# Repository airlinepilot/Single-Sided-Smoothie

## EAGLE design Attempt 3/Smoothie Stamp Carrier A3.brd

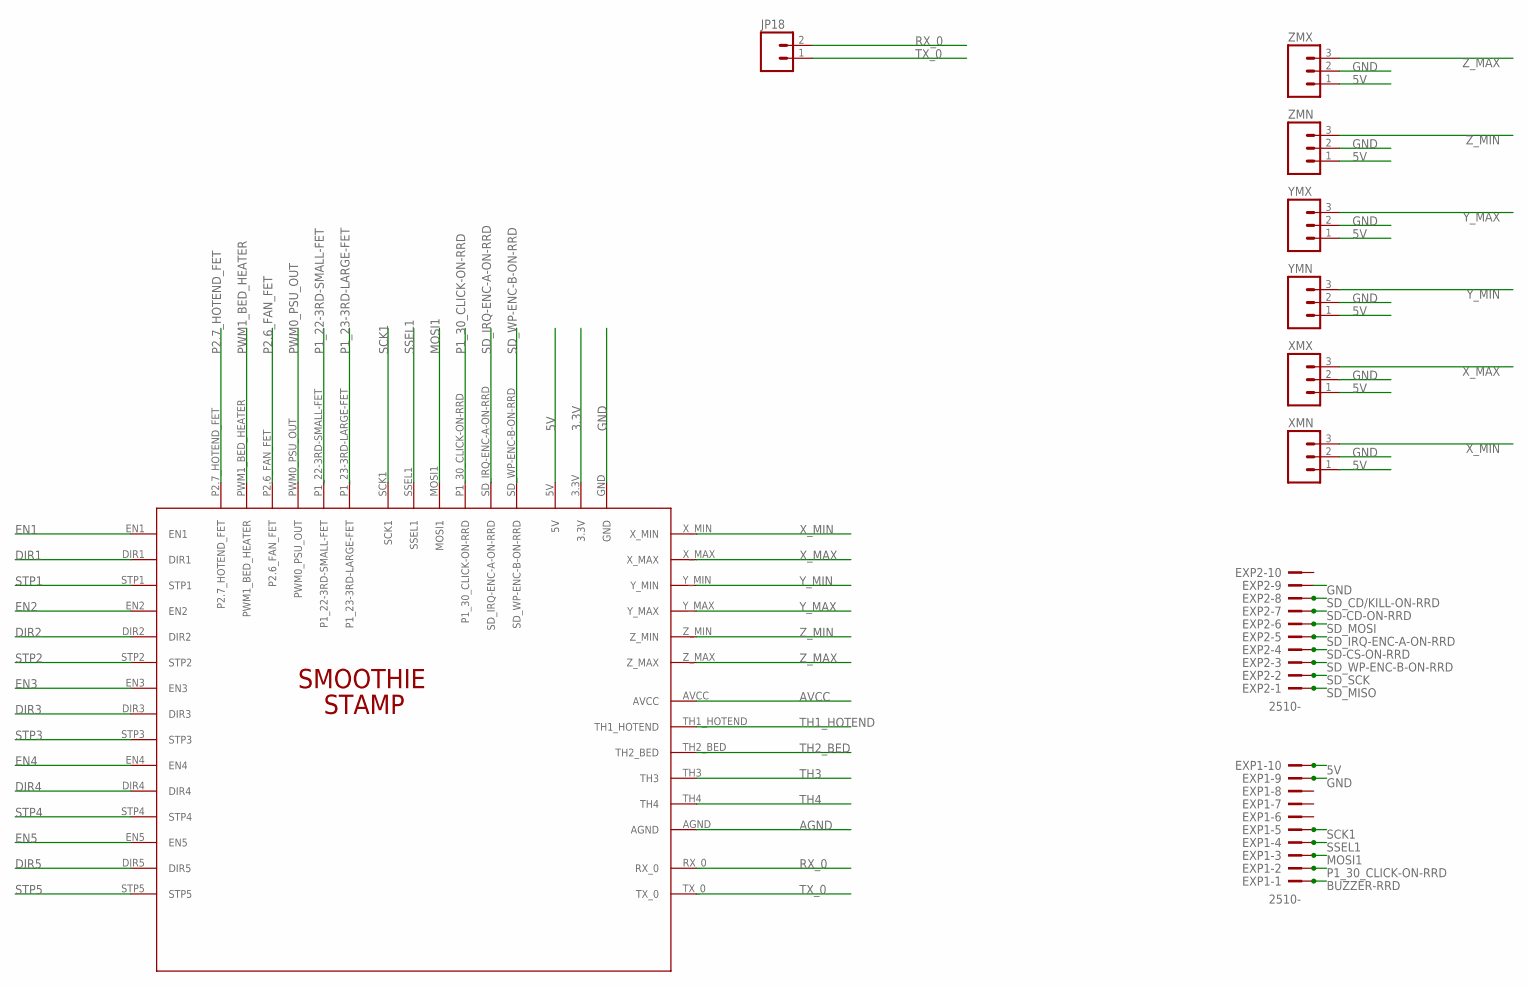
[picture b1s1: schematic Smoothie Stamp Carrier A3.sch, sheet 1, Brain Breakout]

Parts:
EXP1, EXP2: 2510-; PAK100/2500-10
JP18: M02LOCK; 1X02_LOCK
U$1: SMOOTHIE-STAMPSMOOTHIE-STAMP-PTH; SMOOTHIE-STAMP-PTH
XMN: M03LOCK; 1X03_LOCK
XMX: M03LOCK; 1X03_LOCK
YMN: M03LOCK; 1X03_LOCK
YMX: M03LOCK; 1X03_LOCK
ZMN: M03LOCK; 1X03_LOCK
ZMX: M03LOCK; 1X03_LOCK

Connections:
3.3V: U$1.3.3V; also elsewhere on the board
5V: EXP1.10, U$1.5V, XMN.1, XMX.1, YMN.1, YMX.1, ZMN.1, ZMX.1
AGND: U$1.AGND; also elsewhere on the board
AVCC: U$1.AVCC; also elsewhere on the board
BUZZER-RRD: EXP1.1
DIR1: U$1.DIR1; also elsewhere on the board
DIR2: U$1.DIR2; also elsewhere on the board
DIR3: U$1.DIR3; also elsewhere on the board
DIR4: U$1.DIR4; also elsewhere on the board
DIR5: U$1.DIR5; also elsewhere on the board
EN1: U$1.EN1; also elsewhere on the board
EN2: U$1.EN2; also elsewhere on the board
EN3: U$1.EN3; also elsewhere on the board
EN4: U$1.EN4; also elsewhere on the board
EN5: U$1.EN5; also elsewhere on the board
GND: EXP1.9, EXP2.9, U$1.GND, XMN.2, XMX.2, YMN.2, YMX.2, ZMN.2, ZMX.2; also elsewhere on the board
MOSI1: EXP1.3, U$1.MOSI1
P1_22-3RD-SMALL-FET: U$1.P1_22-3RD-SMALL-FET; also elsewhere on the board
P1_23-3RD-LARGE-FET: U$1.P1_23-3RD-LARGE-FET; also elsewhere on the board
P1_30_CLICK-ON-RRD: EXP1.2, U$1.P1_30_CLICK-ON-RRD
P2.6_FAN_FET: U$1.P2.6_FAN_FET; also elsewhere on the board
P2.7_HOTEND_FET: U$1.P2.7_HOTEND_FET; also elsewhere on the board
PWM0_PSU_OUT: U$1.PWM0_PSU_OUT; also elsewhere on the board
PWM1_BED_HEATER: U$1.PWM1_BED_HEATER; also elsewhere on the board
RX_0: JP18.2, U$1.RX_0
SCK1: EXP1.5, U$1.SCK1
SD-CD-ON-RRD: EXP2.7
SD-CS-ON-RRD: EXP2.4
SD_CD/KILL-ON-RRD: EXP2.8
SD_IRQ-ENC-A-ON-RRD: EXP2.5, U$1.SD_IRQ-ENC-A-ON-RRD
SD_MISO: EXP2.1
SD_MOSI: EXP2.6
SD_SCK: EXP2.2
SD_WP-ENC-B-ON-RRD: EXP2.3, U$1.SD_WP-ENC-B-ON-RRD
SSEL1: EXP1.4, U$1.SSEL1
STP1: U$1.STP1; also elsewhere on the board
STP2: U$1.STP2; also elsewhere on the board
STP3: U$1.STP3; also elsewhere on the board
STP4: U$1.STP4; also elsewhere on the board
STP5: U$1.STP5; also elsewhere on the board
TH1_HOTEND: U$1.TH1_HOTEND; also elsewhere on the board
TH2_BED: U$1.TH2_BED; also elsewhere on the board
TH3: U$1.TH3; also elsewhere on the board
TH4: U$1.TH4; also elsewhere on the board
TX_0: JP18.1, U$1.TX_0
X_MAX: U$1.X_MAX, XMX.3
X_MIN: U$1.X_MIN, XMN.3
Y_MAX: U$1.Y_MAX, YMX.3
Y_MIN: U$1.Y_MIN, YMN.3
Z_MAX: U$1.Z_MAX, ZMX.3
Z_MIN: U$1.Z_MIN, ZMN.3

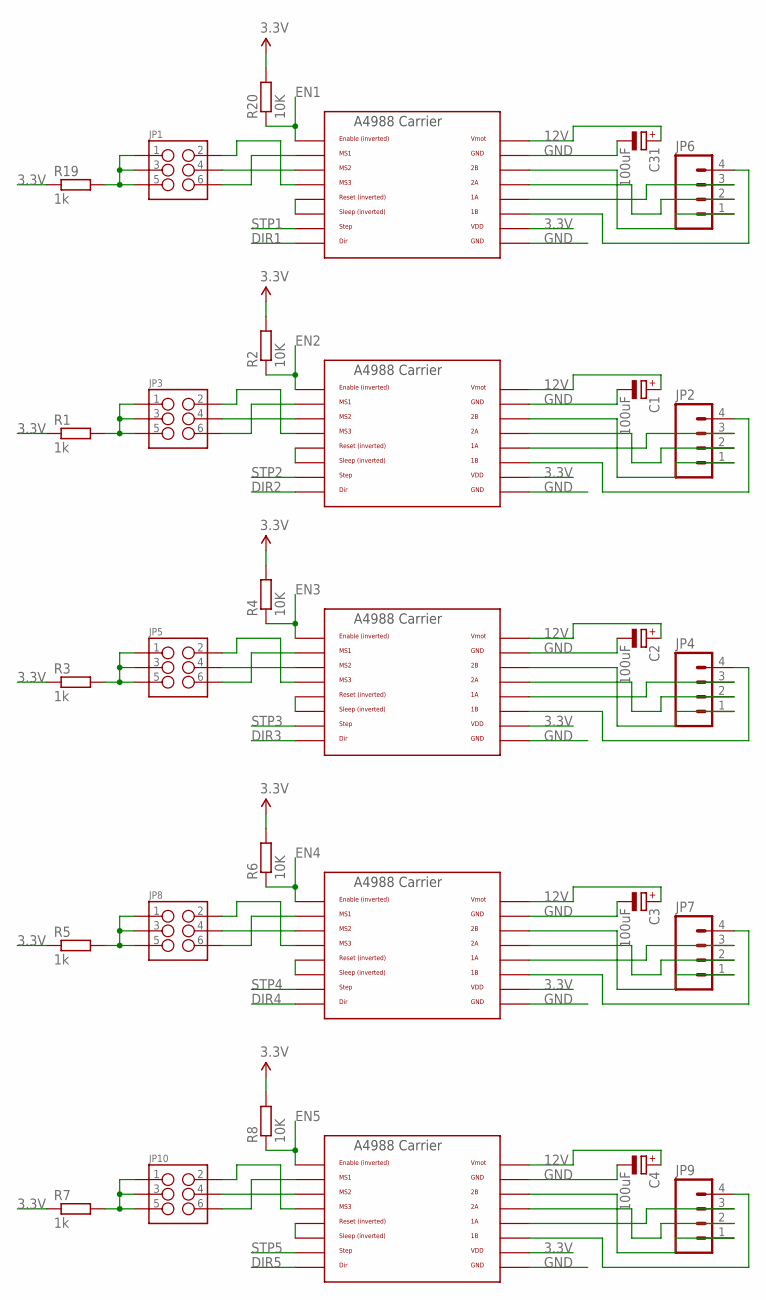
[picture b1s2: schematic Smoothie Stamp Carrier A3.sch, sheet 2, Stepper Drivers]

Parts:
C1, C2, C3, C4, C31: 100uF; E3,5-8
JP1, JP3, JP5, JP8, JP10: M03X22X3_SILK_MALE_PTH; 2X3
JP2, JP4, JP6, JP7, JP9: M04POLAR_LOCK; MOLEX-1X4_LOCK
R1, R3, R5, R7, R19: 1k; 0204V
R2, R4, R6, R8, R20: 10K; 0204V
U$2, U$3, U$4, U$5, U$6: POLOLU_A4983CARRIER; A4988BREAKOUT

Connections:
3.3V: R1.1, R2.2, R3.1, R4.2, R5.1, R6.2, R7.1, R8.2, R19.1, R20.2, U$2.VDD, U$3.VDD, U$4.VDD, U$5.VDD, U$6.VDD; also elsewhere on the board
12V: C1.+, C2.+, C3.+, C4.+, C31.+, U$2.VMOT, U$3.VMOT, U$4.VMOT, U$5.VMOT, U$6.VMOT; also elsewhere on the board
DIR1: U$2.DIR; also elsewhere on the board
DIR2: U$3.DIR; also elsewhere on the board
DIR3: U$4.DIR; also elsewhere on the board
DIR4: U$5.DIR; also elsewhere on the board
DIR5: U$6.DIR; also elsewhere on the board
EN1: R20.1, U$2.EN; also elsewhere on the board
EN2: R2.1, U$3.EN; also elsewhere on the board
EN3: R4.1, U$4.EN; also elsewhere on the board
EN4: R6.1, U$5.EN; also elsewhere on the board
EN5: R8.1, U$6.EN; also elsewhere on the board
GND: C1.-, C2.-, C3.-, C4.-, C31.-, U$2.GND, U$2.GND@0 (GND), U$3.GND, U$3.GND@0 (GND), U$4.GND, U$4.GND@0 (GND), U$5.GND, U$5.GND@0 (GND), U$6.GND, U$6.GND@0 (GND); also elsewhere on the board
unnamed: JP1.6, U$2.MS1
unnamed: JP1.2, U$2.MS3
unnamed: JP1.4, U$2.MS2
unnamed: JP1.1, JP1.3, JP1.5, R19.2
unnamed: JP6.4, U$2.1B
unnamed: JP6.3, U$2.1A
unnamed: JP6.2, U$2.2A
unnamed: JP6.1, U$2.2B
unnamed: U$3.RST, U$3.SLP (SLEEP)
unnamed: JP3.1, JP3.3, JP3.5, R1.2
unnamed: JP3.6, U$3.MS1
unnamed: JP3.2, U$3.MS3
unnamed: JP3.4, U$3.MS2
unnamed: JP2.4, U$3.1B
unnamed: JP2.3, U$3.1A
unnamed: JP2.2, U$3.2A
unnamed: JP2.1, U$3.2B
unnamed: U$4.RST, U$4.SLP (SLEEP)
unnamed: JP5.1, JP5.3, JP5.5, R3.2
unnamed: JP5.6, U$4.MS1
unnamed: JP5.2, U$4.MS3
unnamed: JP5.4, U$4.MS2
unnamed: JP4.4, U$4.1B
unnamed: JP4.3, U$4.1A
unnamed: JP4.2, U$4.2A
unnamed: JP4.1, U$4.2B
unnamed: U$5.RST, U$5.SLP (SLEEP)
unnamed: JP8.1, JP8.3, JP8.5, R5.2
unnamed: JP8.6, U$5.MS1
unnamed: JP8.2, U$5.MS3
unnamed: JP8.4, U$5.MS2
unnamed: JP7.4, U$5.1B
unnamed: JP7.3, U$5.1A
unnamed: JP7.2, U$5.2A
unnamed: U$2.RST, U$2.SLP (SLEEP)
unnamed: JP7.1, U$5.2B
unnamed: U$6.RST, U$6.SLP (SLEEP)
unnamed: JP10.1, JP10.3, JP10.5, R7.2
unnamed: JP10.6, U$6.MS1
unnamed: JP10.2, U$6.MS3
unnamed: JP10.4, U$6.MS2
unnamed: JP9.4, U$6.1B
unnamed: JP9.3, U$6.1A
unnamed: JP9.2, U$6.2A
unnamed: JP9.1, U$6.2B
STP1: U$2.STEP; also elsewhere on the board
STP2: U$3.STEP; also elsewhere on the board
STP3: U$4.STEP; also elsewhere on the board
STP4: U$5.STEP; also elsewhere on the board
STP5: U$6.STEP; also elsewhere on the board

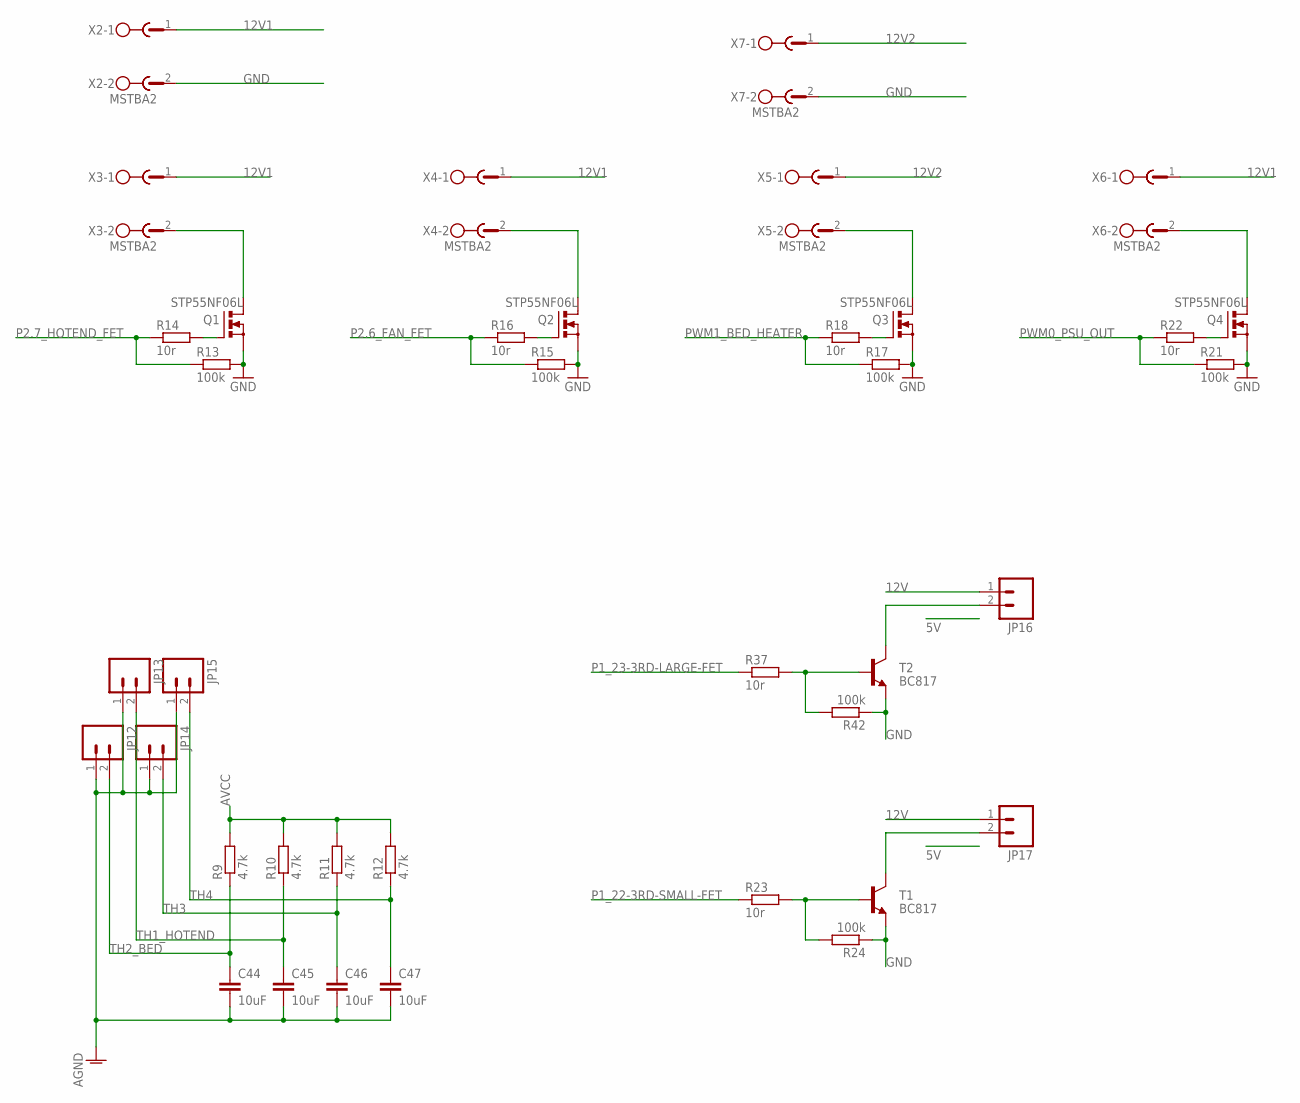
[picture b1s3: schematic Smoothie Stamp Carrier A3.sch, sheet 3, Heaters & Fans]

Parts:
C44, C45, C46, C47: 10uF; C050-025X075
JP12, JP13, JP14, JP15: M02PTH; 1X02
JP16, JP17: M02LOCK; 1X02_LOCK
Q1, Q2, Q3, Q4: STP55NF06L; TO220BV
R9, R10, R11, R12: 4.7k; 0207/5V
R13, R15, R17, R21, R24, R42: 100k; 0204V
R14, R16, R18, R22, R23, R37: 10r; 0204V
T1, T2: BC817; TO-92
X2, X3, X4, X5, X6, X7: MSTBA2

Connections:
12V: JP16.1, JP17.1; also elsewhere on the board
12V1: X2.1, X3.1, X4.1, X6.1
12V2: X5.1, X7.1
AGND: C44.2, C45.2, C46.2, C47.2, JP12.1, JP13.1, JP14.1, JP15.1; also elsewhere on the board
AVCC: R9.2, R10.2, R11.2, R12.2; also elsewhere on the board
GND: Q1.S, Q2.S, Q3.S, Q4.S, R13.2, R15.2, R17.2, R21.2, R24.1, R42.1, T1.1 (E), T2.1 (E), X2.2, X7.2; also elsewhere on the board
unnamed: Q1.D, X3.2
unnamed: Q2.G, R16.2
unnamed: Q2.D, X4.2
unnamed: Q3.G, R18.2
unnamed: Q3.D, X5.2
unnamed: Q4.G, R22.2
unnamed: Q4.D, X6.2
unnamed: Q1.G, R14.2
unnamed: JP16.2, T2.3 (C)
unnamed: R37.2, R42.2, T2.2 (B)
unnamed: JP17.2, T1.3 (C)
unnamed: R23.2, R24.2, T1.2 (B)
P1_22-3RD-SMALL-FET: R23.1; also elsewhere on the board
P1_23-3RD-LARGE-FET: R37.1; also elsewhere on the board
P2.6_FAN_FET: R15.1, R16.1; also elsewhere on the board
P2.7_HOTEND_FET: R13.1, R14.1; also elsewhere on the board
PWM0_PSU_OUT: R21.1, R22.1; also elsewhere on the board
PWM1_BED_HEATER: R17.1, R18.1; also elsewhere on the board
TH1_HOTEND: C45.1, JP13.2, R10.1; also elsewhere on the board
TH2_BED: C44.1, JP12.2, R9.1; also elsewhere on the board
TH3: C46.1, JP14.2, R11.1; also elsewhere on the board
TH4: C47.1, JP15.2, R12.1; also elsewhere on the board

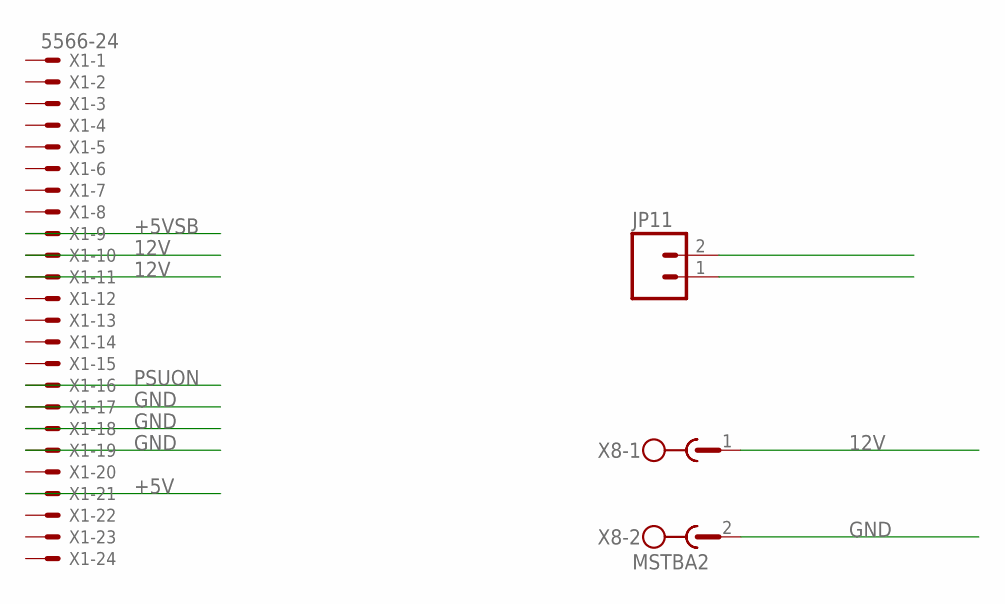
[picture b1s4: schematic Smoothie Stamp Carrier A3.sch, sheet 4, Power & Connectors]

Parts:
JP11: M02LOCK; 1X02_LOCK
X1: 5566-24
X8: MSTBA2

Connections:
12V: X1.10, X1.11, X8.1; also elsewhere on the board
+5V: X1.21
+5VSB: X1.9
GND: JP11.1, X1.17, X1.18, X1.19, X8.2; also elsewhere on the board
PSUON: JP11.2, X1.16

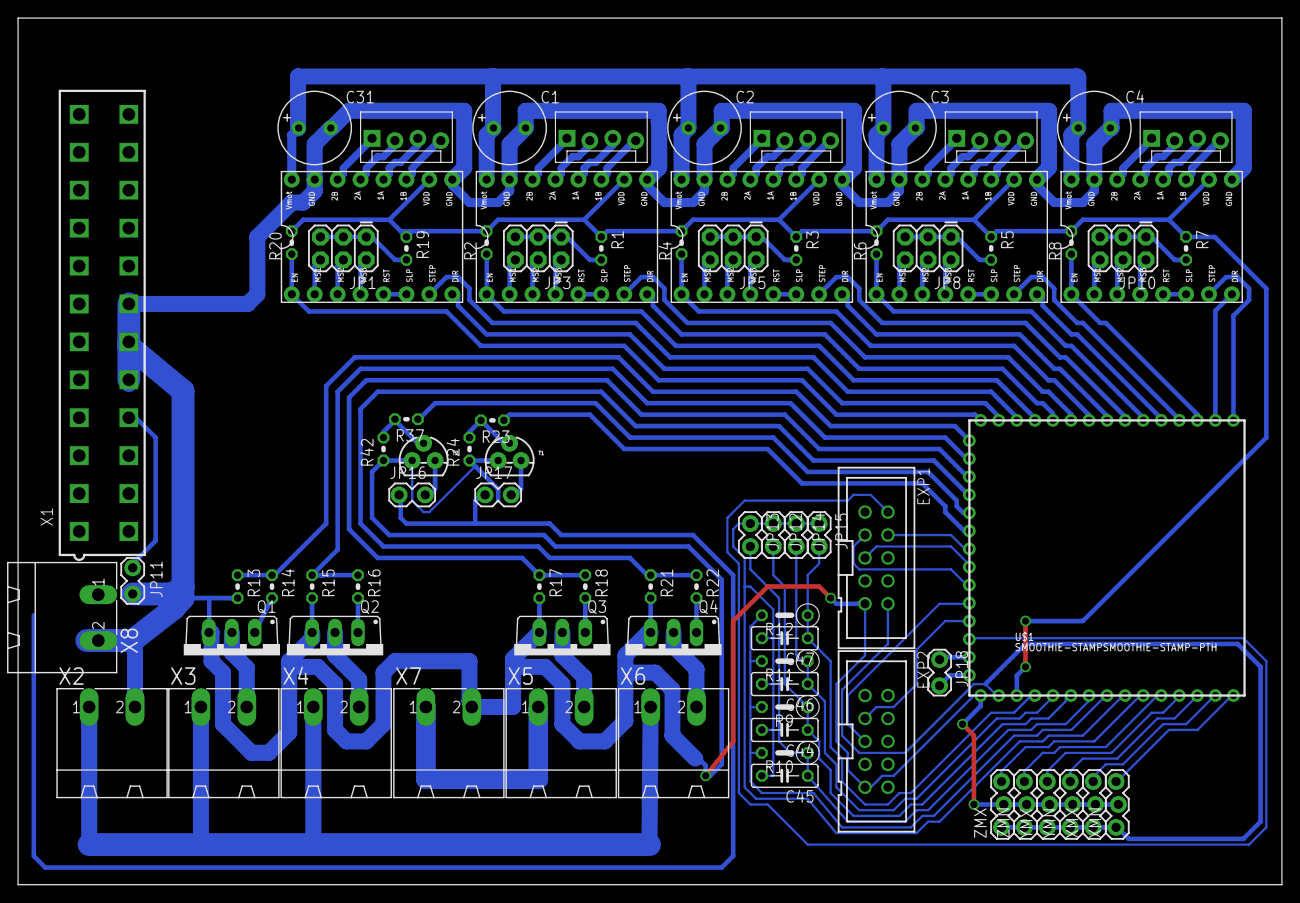
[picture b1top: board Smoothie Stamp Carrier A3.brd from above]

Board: 2 copper layers, 140.0 x 96.0 mm, 81 parts (0 on the bottom side), 105 nets.

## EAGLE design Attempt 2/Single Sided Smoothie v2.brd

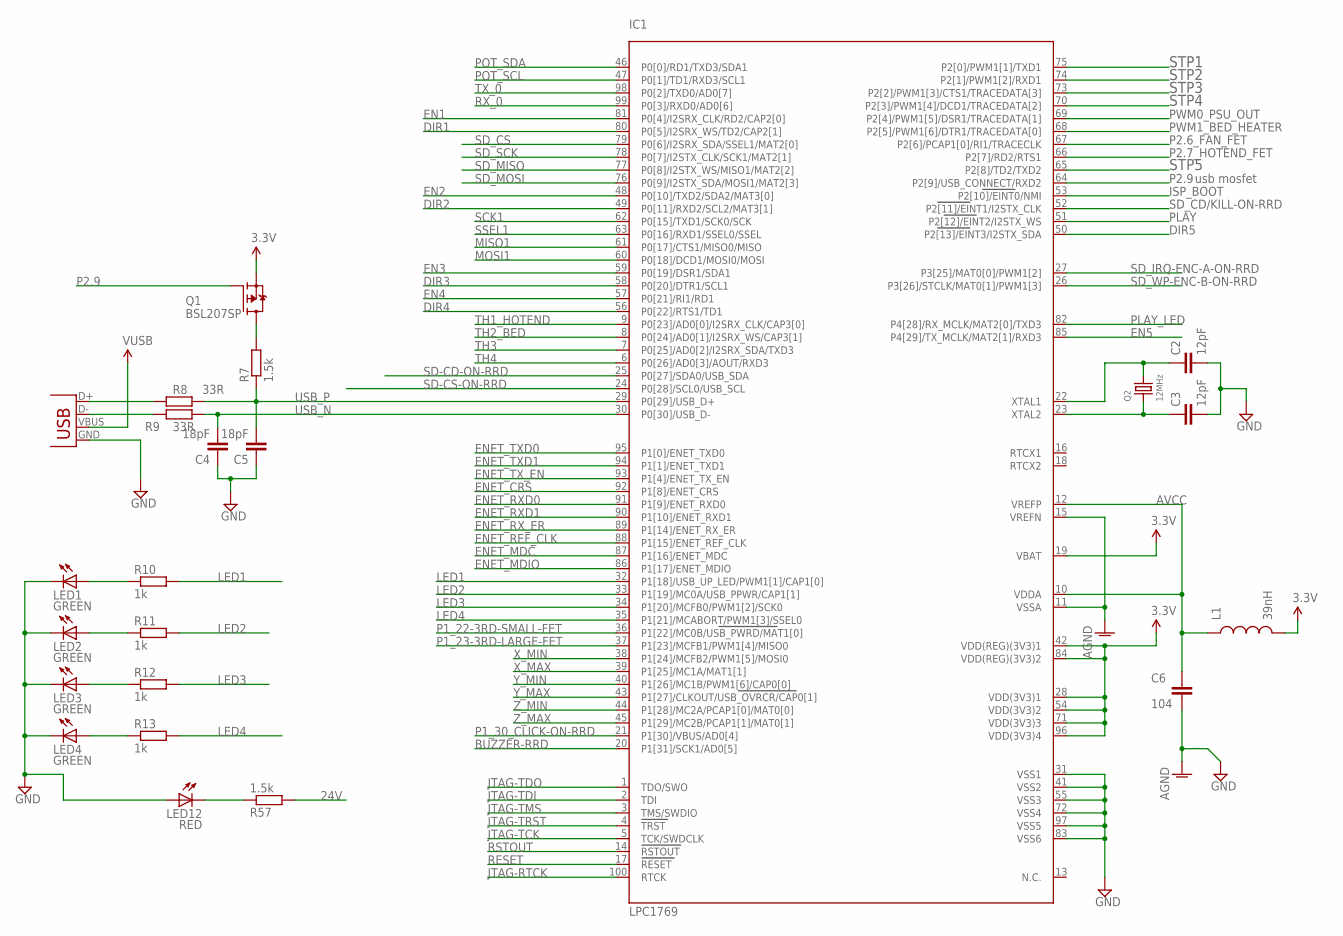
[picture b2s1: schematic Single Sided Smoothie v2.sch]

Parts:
C2, C3: 12pF; C0603
C4, C5: 18pF; C0603
C6: 104; C0603
IC1: LPC1769; LQFP100
L1: 39nH; 0603
LED1, LED2, LED3, LED4: GREEN; SML0603
LED12: RED; SML0603
Q1: BSL207SP; SC74_INFINEON
Q2: 12MHz; CRYSTAL_3.2X2.5
R7, R57: 1.5k; R0603
R8, R9: 33R; R0603
R10, R11, R12, R13: 1k; R0603
X14: USBPTH; USB-B-PTH

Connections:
3.3V: IC1.19 (VBAT), IC1.28 (VDD(3V3)1), IC1.42 (VDD(REG)(3V3)1), IC1.54 (VDD(3V3)2), IC1.71 (VDD(3V3)3), IC1.84 (VDD(REG)(3V3)2), IC1.96 (VDD(3V3)4), L1.2, Q1.4 (S)
24V: R57.2
AGND: C6.2, IC1.11 (VSSA), IC1.15 (VREFN)
AVCC: C6.1, IC1.10 (VDDA), IC1.12 (VREFP), L1.1
BUZZER-RRD: IC1.20 (P1[31]/SCK1/AD0[5])
DIR1: IC1.80 (P0[5]/I2SRX_WS/TD2/CAP2[1])
DIR2: IC1.49 (P0[11]/RXD2/SCL2/MAT3[1])
DIR3: IC1.58 (P0[20]/DTR1/SCL1)
DIR4: IC1.56 (P0[22]/RTS1/TD1)
DIR5: IC1.50 (P2[13]/EINT3/I2STX_SDA)
EN1: IC1.81 (P0[4]/I2SRX_CLK/RD2/CAP2[0])
EN2: IC1.48 (P0[10]/TXD2/SDA2/MAT3[0])
EN3: IC1.59 (P0[19]/DSR1/SDA1)
EN4: IC1.57 (P0[21]/RI1/RD1)
EN5: IC1.85 (P4[29]/TX_MCLK/MAT2[1]/RXD3)
ENET_CRS: IC1.92 (P1[8]/ENET_CRS)
ENET_MDC: IC1.87 (P1[16]/ENET_MDC)
ENET_MDIO: IC1.86 (P1[17]/ENET_MDIO)
ENET_REF_CLK: IC1.88 (P1[15]/ENET_REF_CLK)
ENET_RXD0: IC1.91 (P1[9]/ENET_RXD0)
ENET_RXD1: IC1.90 (P1[10]/ENET_RXD1)
ENET_RX_ER: IC1.89 (P1[14]/ENET_RX_ER)
ENET_TXD0: IC1.95 (P1[0]/ENET_TXD0)
ENET_TXD1: IC1.94 (P1[1]/ENET_TXD1)
ENET_TX_EN: IC1.93 (P1[4]/ENET_TX_EN)
GND: C2.2, C3.2, C4.1, C5.1, IC1.31 (VSS1), IC1.41 (VSS2), IC1.55 (VSS3), IC1.72 (VSS4), IC1.83 (VSS6), IC1.97 (VSS5), LED1.C, LED2.C, LED3.C, LED4.C, LED12.A, X14.GND
ISP_BOOT: IC1.53 (P2[10]/EINT0/NMI)
JTAG-RTCK: IC1.100 (RTCK)
JTAG-TCK: IC1.5 (TCK/SWDCLK)
JTAG-TDI: IC1.2 (TDI)
JTAG-TDO: IC1.1 (TDO/SWO)
JTAG-TMS: IC1.3 (TMS/SWDIO)
JTAG-TRST: IC1.4 (TRST)
LED1: IC1.32 (P1[18]/USB_UP_LED/PWM1[1]/CAP1[0]), R10.2
LED2: IC1.33 (P1[19]/MC0A/USB_PPWR/CAP1[1]), R11.2
LED3: IC1.34 (P1[20]/MCFB0/PWM1[2]/SCK0), R12.2
LED4: IC1.35 (P1[21]/MCABORT/PWM1[3]/SSEL0), R13.2
MISO1: IC1.61 (P0[17]/CTS1/MISO0/MISO)
MOSI1: IC1.60 (P0[18]/DCD1/MOSI0/MOSI)
unnamed: C2.1, IC1.22 (XTAL1), Q2.2
unnamed: C3.1, IC1.23 (XTAL2), Q2.1
unnamed: LED12.C, R57.1
unnamed: Q1.1 (D), Q1.2 (D), Q1.5 (D), Q1.6 (D), R7.2
unnamed: R8.1, X14.D+
unnamed: R9.1, X14.D-
unnamed: LED4.A, R13.1
unnamed: LED3.A, R12.1
unnamed: LED2.A, R11.1
unnamed: LED1.A, R10.1
P1_22-3RD-SMALL-FET: IC1.36 (P1[22]/MC0B/USB_PWRD/MAT1[0])
P1_23-3RD-LARGE-FET: IC1.37 (P1[23]/MCFB1/PWM1[4]/MISO0)
P1_30_CLICK-ON-RRD: IC1.21 (P1[30]/VBUS/AD0[4])
P2.6_FAN_FET: IC1.67 (P2[6]/PCAP1[0]/RI1/TRACECLK)
P2.7_HOTEND_FET: IC1.66 (P2[7]/RD2/RTS1)
P2.9: IC1.64 (P2[9]/USB_CONNECT/RXD2), Q1.3 (G)
PLAY: IC1.51 (P2[12]/EINT2/I2STX_WS)
PLAY_LED: IC1.82 (P4[28]/RX_MCLK/MAT2[0]/TXD3)
POT_SCL: IC1.47 (P0[1]/TD1/RXD3/SCL1)
POT_SDA: IC1.46 (P0[0]/RD1/TXD3/SDA1)
PWM0_PSU_OUT: IC1.69 (P2[4]/PWM1[5]/DSR1/TRACEDATA[1])
PWM1_BED_HEATER: IC1.68 (P2[5]/PWM1[6]/DTR1/TRACEDATA[0])
RESET: IC1.17 (RESET)
RSTOUT: IC1.14 (RSTOUT)
RX_0: IC1.99 (P0[3]/RXD0/AD0[6])
SCK1: IC1.62 (P0[15]/TXD1/SCK0/SCK)
SD-CD-ON-RRD: IC1.25 (P0[27]/SDA0/USB_SDA)
SD-CS-ON-RRD: IC1.24 (P0[28]/SCL0/USB_SCL)
SD_CD/KILL-ON-RRD: IC1.52 (P2[11]/EINT1/I2STX_CLK)
SD_CS: IC1.79 (P0[6]/I2SRX_SDA/SSEL1/MAT2[0])
SD_IRQ-ENC-A-ON-RRD: IC1.27 (P3[25]/MAT0[0]/PWM1[2])
SD_MISO: IC1.77 (P0[8]/I2STX_WS/MISO1/MAT2[2])
SD_MOSI: IC1.76 (P0[9]/I2STX_SDA/MOSI1/MAT2[3])
SD_SCK: IC1.78 (P0[7]/I2STX_CLK/SCK1/MAT2[1])
SD_WP-ENC-B-ON-RRD: IC1.26 (P3[26]/STCLK/MAT0[1]/PWM1[3])
SSEL1: IC1.63 (P0[16]/RXD1/SSEL0/SSEL)
STP1: IC1.75 (P2[0]/PWM1[1]/TXD1)
STP2: IC1.74 (P2[1]/PWM1[2]/RXD1)
STP3: IC1.73 (P2[2]/PWM1[3]/CTS1/TRACEDATA[3])
STP4: IC1.70 (P2[3]/PWM1[4]/DCD1/TRACEDATA[2])
STP5: IC1.65 (P2[8]/TD2/TXD2)
TH1_HOTEND: IC1.9 (P0[23]/AD0[0]/I2SRX_CLK/CAP3[0])
TH2_BED: IC1.8 (P0[24]/AD0[1]/I2SRX_WS/CAP3[1])
TH3: IC1.7 (P0[25]/AD0[2]/I2SRX_SDA/TXD3)
TH4: IC1.6 (P0[26]/AD0[3]/AOUT/RXD3)
TX_0: IC1.98 (P0[2]/TXD0/AD0[7])
USB_N: C4.2, IC1.30 (P0[30]/USB_D-), R9.2
USB_P: C5.2, IC1.29 (P0[29]/USB_D+), R7.1, R8.2
VUSB: X14.VBUS
X_MAX: IC1.39 (P1[25]/MC1A/MAT1[1])
X_MIN: IC1.38 (P1[24]/MCFB2/PWM1[5]/MOSI0)
Y_MAX: IC1.43 (P1[27]/CLKOUT/USB_OVRCR/CAP0[1])
Y_MIN: IC1.40 (P1[26]/MC1B/PWM1[6]/CAP0[0])
Z_MAX: IC1.45 (P1[29]/MC2B/PCAP1[1]/MAT0[1])
Z_MIN: IC1.44 (P1[28]/MC2A/PCAP1[0]/MAT0[0])

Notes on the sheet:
usb mosfet

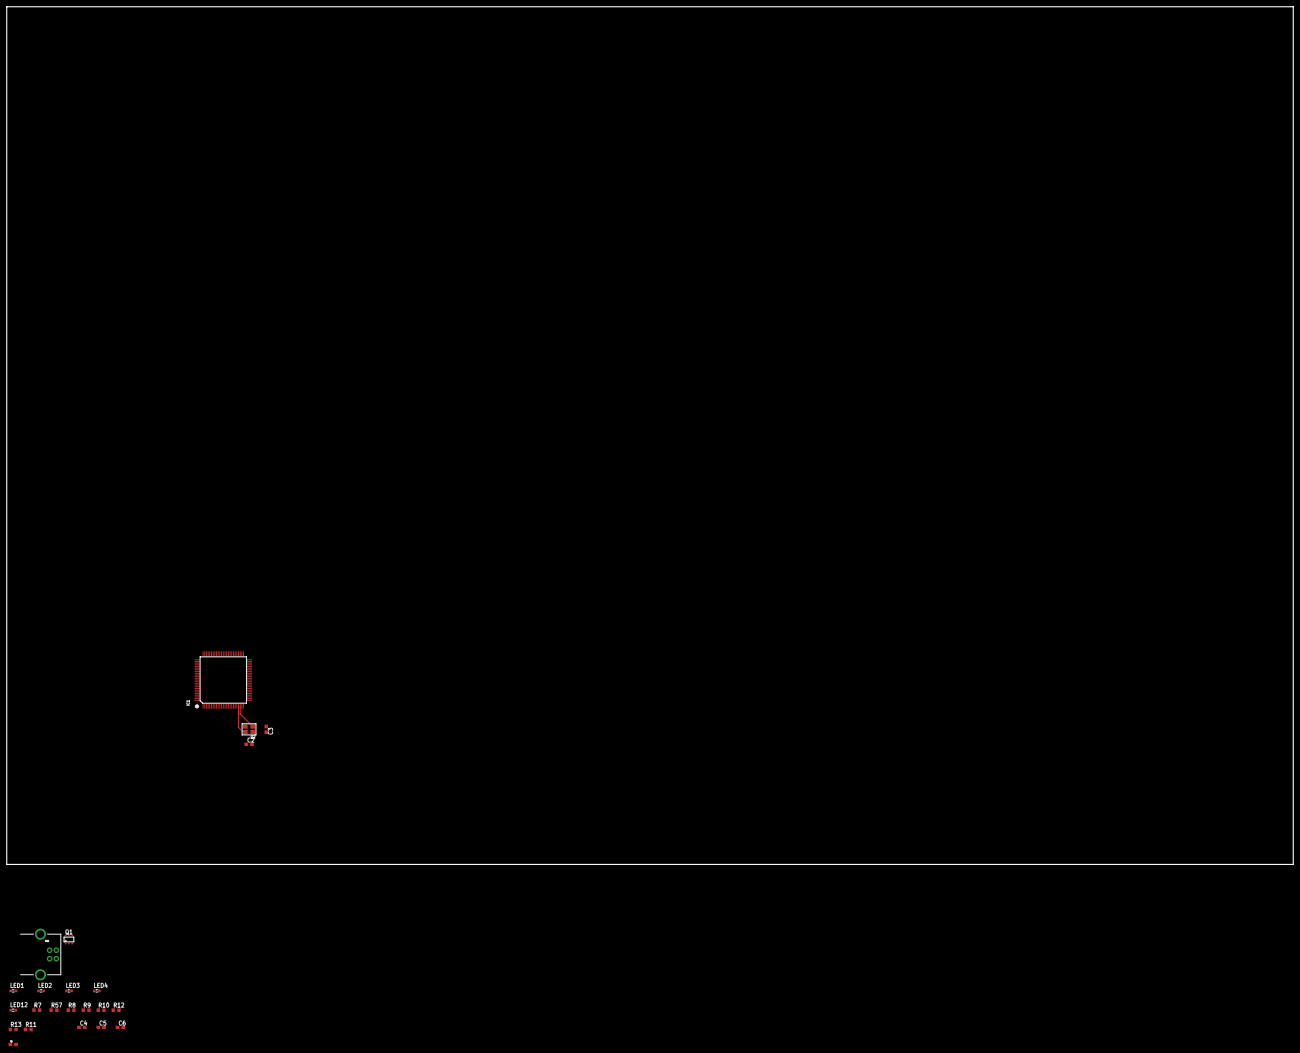
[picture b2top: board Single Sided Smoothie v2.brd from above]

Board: 2 copper layers, 381.0 x 254.0 mm, 23 parts (0 on the bottom side), 21 nets.

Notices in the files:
parts and their libraries:
SparkFun-Connectors: Licensing: Creative Commons ShareAlike 4.0 International - https://creativecommons.org/licenses/by-sa/4.0
SparkFun-Passives: Licensing: CC v3.0 Share-Alike You are welcome to use this library for commercial purposes.
